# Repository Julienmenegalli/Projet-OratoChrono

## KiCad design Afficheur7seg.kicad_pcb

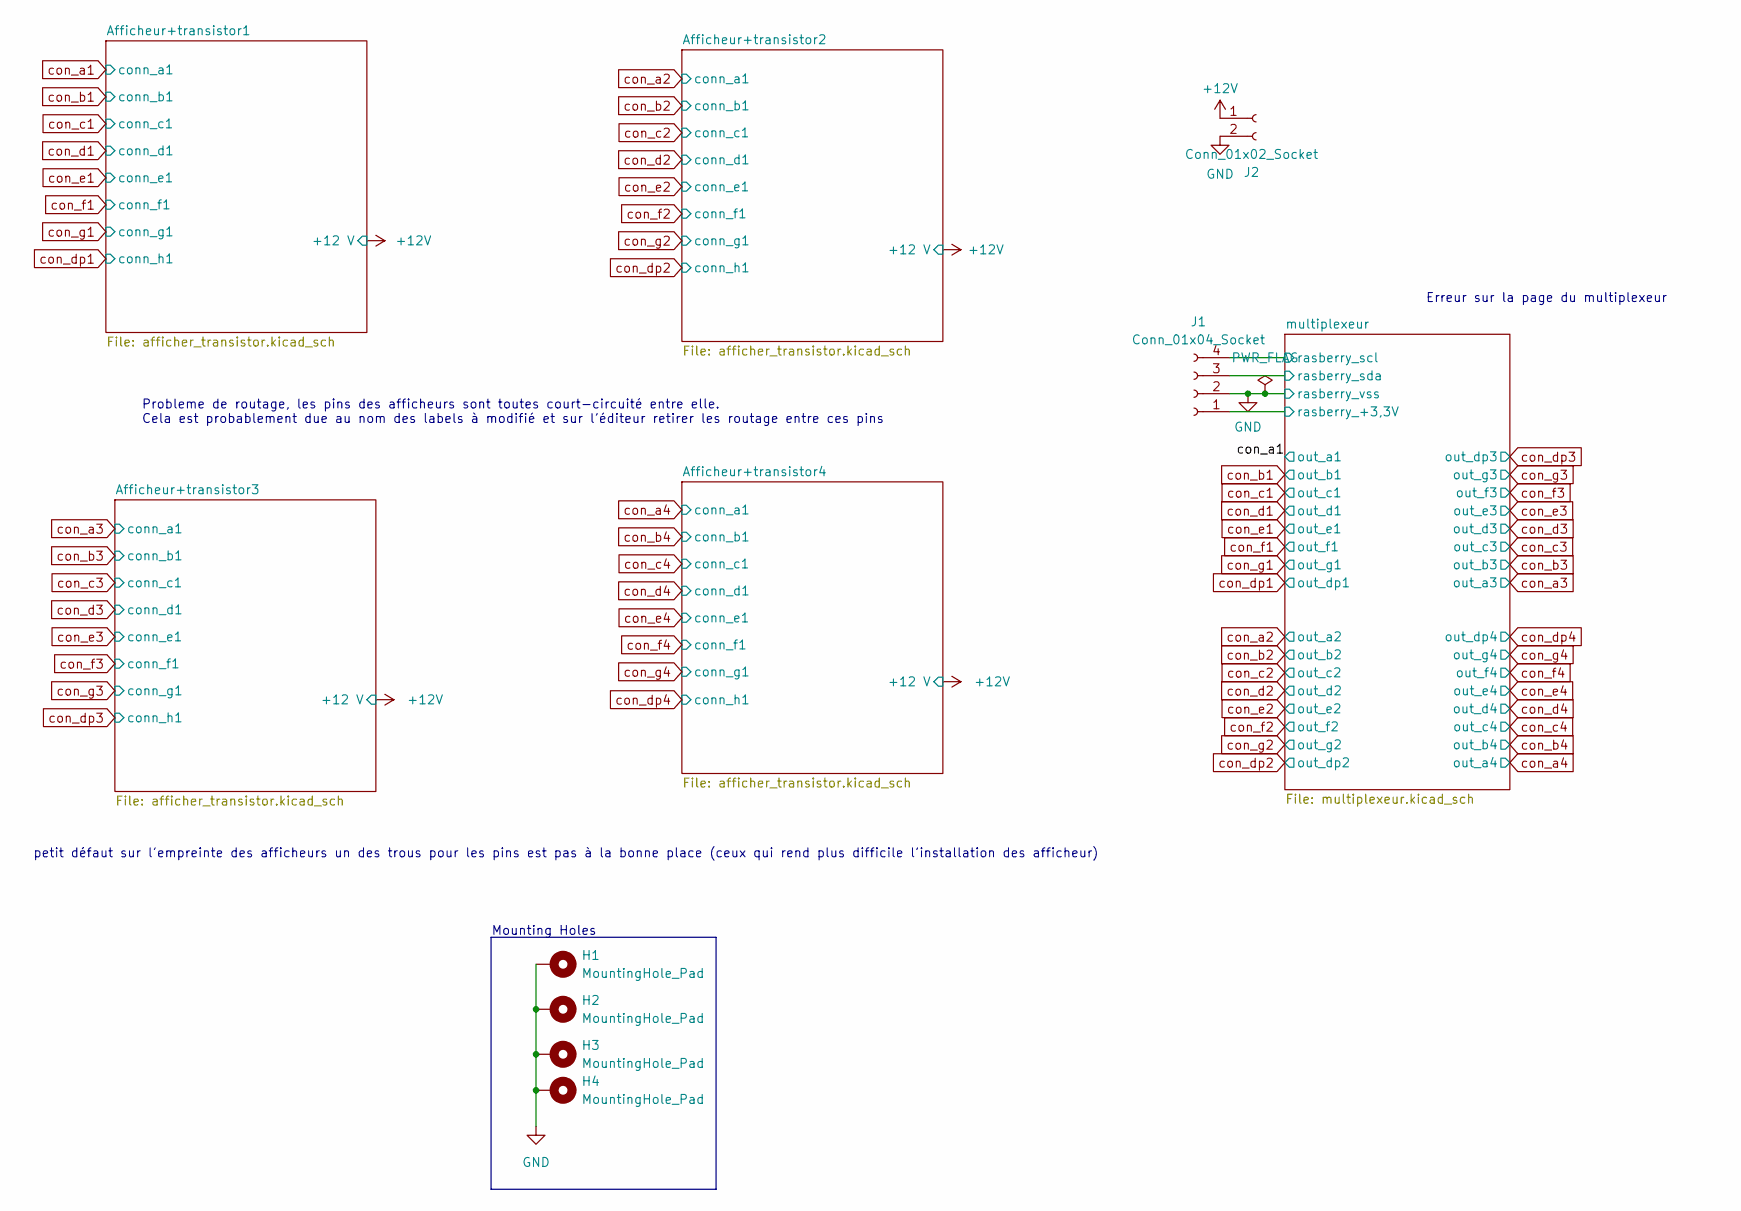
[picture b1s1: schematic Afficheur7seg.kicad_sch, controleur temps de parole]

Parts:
H1, H2, H3, H4: MountingHole_Pad; MountingHole_3.2mm_M3_DIN965_Pad
J1: Conn_01x04_Socket; JST_XH_B4B-XH-A_1x04_P2.50mm_Vertical
J2: Conn_01x02_Socket; JST_XH_B2B-XH-A_1x02_P2.50mm_Vertical

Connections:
+12V: J2.1; also elsewhere on the board
/multiplexeur/rasberry_+3,3V: J1.1; also elsewhere on the board
/multiplexeur/rasberry_scl: J1.4; also elsewhere on the board
/multiplexeur/rasberry_sda: J1.3; also elsewhere on the board
GND: H1.1, H2.1, H3.1, H4.1, J1.2, J2.2; also elsewhere on the board

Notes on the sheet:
petit défaut sur l'empreinte des afficheurs un des trous pour les pins est pas à la bonne place (ceux qui rend plus difficile l'installation des afficheur)
Probleme de routage, les pins des afficheurs sont toutes court-circuité entre elle. Cela est probablement due au nom des labels à modifié et sur l'éditeur retirer les routage entre ces pins
Mounting Holes
Erreur sur la page du multiplexeur

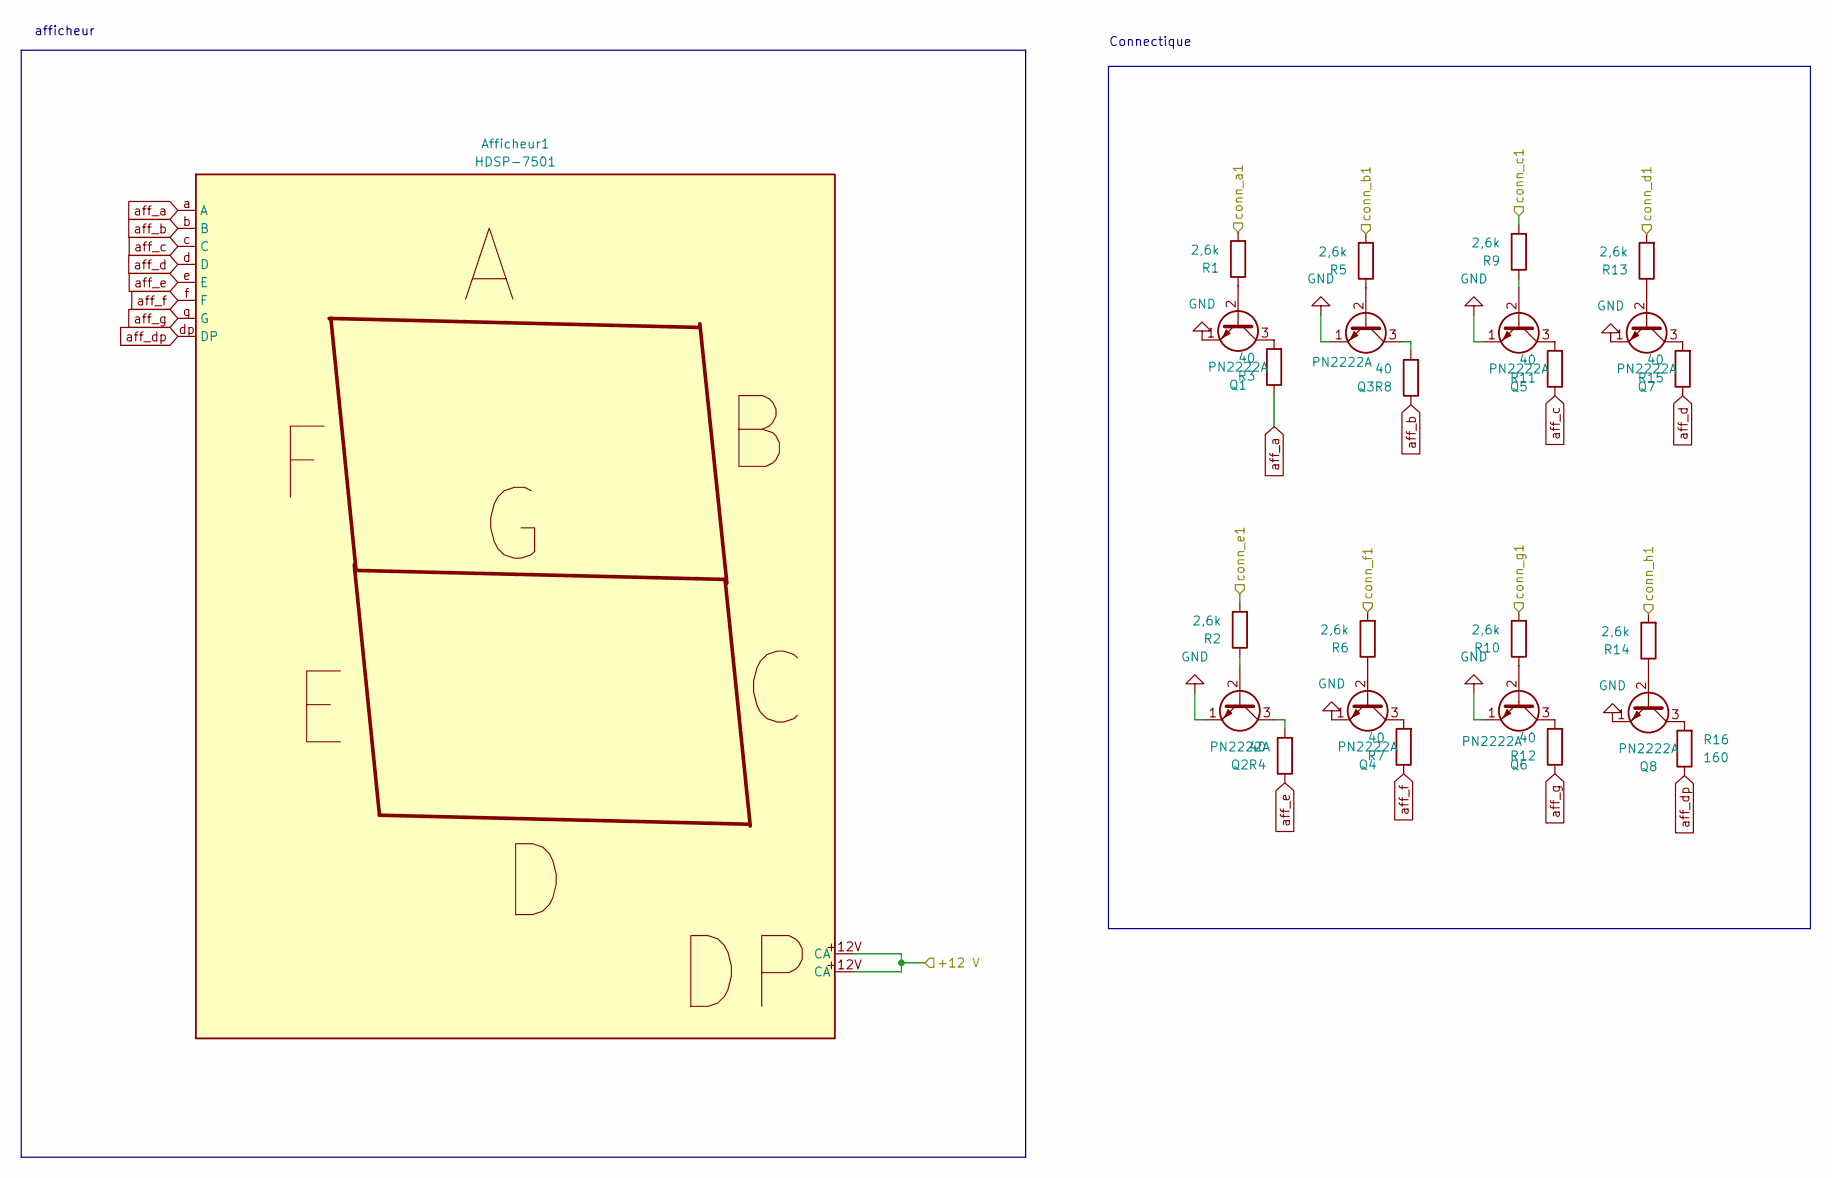
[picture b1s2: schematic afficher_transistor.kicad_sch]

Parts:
Afficheur1: HDSP-7501; Aff_7seg_footprint
Q1, Q2, Q3, Q4, Q5, Q6, Q7, Q8: PN2222A; TO-92_Inline
R1, R2, R5, R6, R9, R10, R13, R14: 2,6k; R_0805_2012Metric
R3, R4, R7, R8, R11, R12, R15: 40; R_Axial_DIN0414_L11.9mm_D4.5mm_P15.24mm_Horizontal
R16: 160; R_Axial_DIN0414_L11.9mm_D4.5mm_P15.24mm_Horizontal

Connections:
+12V: Afficheur1.+12V (CA); also elsewhere on the board
GND: Q1.1 (E), Q2.1 (E), Q3.1 (E), Q4.1 (E), Q5.1 (E), Q6.1 (E), Q7.1 (E), Q8.1 (E); also elsewhere on the board
unnamed: Q1.2 (B), R1.1
unnamed: Q1.3 (C), R3.2
unnamed: Q2.2 (B), R2.1
unnamed: Q2.3 (C), R4.2
unnamed: Q3.2 (B), R5.1
unnamed: Q3.3 (C), R8.2
unnamed: Q4.2 (B), R6.1
unnamed: Q4.3 (C), R7.2
unnamed: Q5.2 (B), R9.1
unnamed: Q5.3 (C), R11.2
unnamed: Q6.2 (B), R10.1
unnamed: Q6.3 (C), R12.2
unnamed: Q7.2 (B), R13.1
unnamed: Q7.3 (C), R15.2
unnamed: Q8.2 (B), R14.1
unnamed: Q8.3 (C), R16.2
aff_a: Afficheur1.a (A), R3.1; also elsewhere on the board
aff_b: Afficheur1.b (B), R8.1; also elsewhere on the board
aff_c: Afficheur1.c (C), R11.1; also elsewhere on the board
aff_d: Afficheur1.d (D), R15.1; also elsewhere on the board
aff_dp: Afficheur1.dp (DP), R16.1; also elsewhere on the board
aff_e: Afficheur1.e (E), R4.1; also elsewhere on the board
aff_f: Afficheur1.f (F), R7.1; also elsewhere on the board
aff_g: Afficheur1.g (G), R12.1; also elsewhere on the board
con_a2: R1.2; also elsewhere on the board
con_b2: R5.2; also elsewhere on the board
con_c2: R9.2; also elsewhere on the board
con_d2: R13.2; also elsewhere on the board
con_dp2: R14.2; also elsewhere on the board
con_e2: R2.2; also elsewhere on the board
con_f2: R6.2; also elsewhere on the board
con_g2: R10.2; also elsewhere on the board

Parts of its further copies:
Afficheur2, Afficheur3, Afficheur4: HDSP-7501; Aff_7seg_footprint
Q9, Q10, Q11, Q12, Q13, Q14, Q15, Q16, Q17, Q18, Q19, Q20, Q21, Q22, Q23, Q24, Q25, Q26, Q27, Q28, Q29, Q30, Q31, Q32: PN2222A; TO-92_Inline
R17, R18, R21, R22, R25, R26, R29, R30, R33, R34, R37, R38, R41, R42, R45, R46, R51, R52, R55, R56, R59, R60, R63, R64: 2,6k; R_0805_2012Metric
R19, R20, R23, R24, R27, R28, R31, R35, R36, R39, R40, R43, R44, R47, R53, R54, R57, R58, R61, R62, R65: 40; R_Axial_DIN0414_L11.9mm_D4.5mm_P15.24mm_Horizontal
R32, R48, R66: 160; R_Axial_DIN0414_L11.9mm_D4.5mm_P15.24mm_Horizontal

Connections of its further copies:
+12V: Afficheur2.+12V (CA), Afficheur3.+12V (CA), Afficheur4.+12V (CA); also elsewhere on the board
GND: Q9.1 (E), Q10.1 (E), Q11.1 (E), Q12.1 (E), Q13.1 (E), Q14.1 (E), Q15.1 (E), Q16.1 (E), Q17.1 (E), Q18.1 (E), Q19.1 (E), Q20.1 (E), Q21.1 (E), Q22.1 (E), Q23.1 (E), Q24.1 (E), Q25.1 (E), Q26.1 (E), Q27.1 (E), Q28.1 (E), Q29.1 (E), Q30.1 (E), Q31.1 (E), Q32.1 (E); also elsewhere on the board
unnamed: Q9.2 (B), R17.1
unnamed: Q9.3 (C), R19.2
unnamed: Q10.2 (B), R18.1
unnamed: Q10.3 (C), R20.2
unnamed: Q11.2 (B), R21.1
unnamed: Q11.3 (C), R24.2
unnamed: Q12.2 (B), R22.1
unnamed: Q12.3 (C), R23.2
unnamed: Q13.2 (B), R25.1
unnamed: Q13.3 (C), R27.2
unnamed: Q14.2 (B), R26.1
unnamed: Q14.3 (C), R28.2
unnamed: Q15.2 (B), R29.1
unnamed: Q15.3 (C), R31.2
unnamed: Q16.2 (B), R30.1
unnamed: Q16.3 (C), R32.2
unnamed: Q17.2 (B), R33.1
unnamed: Q17.3 (C), R35.2
unnamed: Q18.2 (B), R34.1
unnamed: Q18.3 (C), R36.2
unnamed: Q19.2 (B), R37.1
unnamed: Q19.3 (C), R40.2
unnamed: Q20.2 (B), R38.1
unnamed: Q20.3 (C), R39.2
unnamed: Q21.2 (B), R41.1
unnamed: Q21.3 (C), R43.2
unnamed: Q22.2 (B), R42.1
unnamed: Q22.3 (C), R44.2
unnamed: Q23.2 (B), R45.1
unnamed: Q23.3 (C), R47.2
unnamed: Q24.2 (B), R46.1
unnamed: Q24.3 (C), R48.2
unnamed: Q25.2 (B), R51.1
unnamed: Q25.3 (C), R53.2
unnamed: Q26.2 (B), R52.1
unnamed: Q26.3 (C), R54.2
unnamed: Q27.2 (B), R55.1
unnamed: Q27.3 (C), R58.2
unnamed: Q28.2 (B), R56.1
unnamed: Q28.3 (C), R57.2
unnamed: Q29.2 (B), R59.1
unnamed: Q29.3 (C), R61.2
unnamed: Q30.2 (B), R60.1
unnamed: Q30.3 (C), R62.2
unnamed: Q31.2 (B), R63.1
unnamed: Q31.3 (C), R65.2
unnamed: Q32.2 (B), R64.1
unnamed: Q32.3 (C), R66.2
aff_a: Afficheur2.a (A), Afficheur3.a (A), Afficheur4.a (A), R19.1, R35.1, R53.1; also elsewhere on the board
aff_b: Afficheur2.b (B), Afficheur3.b (B), Afficheur4.b (B), R24.1, R40.1, R58.1; also elsewhere on the board
aff_c: Afficheur2.c (C), Afficheur3.c (C), Afficheur4.c (C), R27.1, R43.1, R61.1; also elsewhere on the board
aff_d: Afficheur2.d (D), Afficheur3.d (D), Afficheur4.d (D), R31.1, R47.1, R65.1; also elsewhere on the board
aff_dp: Afficheur2.dp (DP), Afficheur3.dp (DP), Afficheur4.dp (DP), R32.1, R48.1, R66.1; also elsewhere on the board
aff_e: Afficheur2.e (E), Afficheur3.e (E), Afficheur4.e (E), R20.1, R36.1, R54.1; also elsewhere on the board
aff_f: Afficheur2.f (F), Afficheur3.f (F), Afficheur4.f (F), R23.1, R39.1, R57.1; also elsewhere on the board
aff_g: Afficheur2.g (G), Afficheur3.g (G), Afficheur4.g (G), R28.1, R44.1, R62.1; also elsewhere on the board
con_a1: R51.2; also elsewhere on the board
con_a3: R17.2; also elsewhere on the board
con_a4: R33.2; also elsewhere on the board
con_b1: R55.2; also elsewhere on the board
con_b3: R21.2; also elsewhere on the board
con_b4: R37.2; also elsewhere on the board
con_c1: R59.2; also elsewhere on the board
con_c3: R25.2; also elsewhere on the board
con_c4: R41.2; also elsewhere on the board
con_d1: R63.2; also elsewhere on the board
con_d3: R29.2; also elsewhere on the board
con_d4: R45.2; also elsewhere on the board
con_dp1: R64.2; also elsewhere on the board
con_dp3: R30.2; also elsewhere on the board
con_dp4: R46.2; also elsewhere on the board
con_e1: R52.2; also elsewhere on the board
con_e3: R18.2; also elsewhere on the board
con_e4: R34.2; also elsewhere on the board
con_f1: R56.2; also elsewhere on the board
con_f3: R22.2; also elsewhere on the board
con_f4: R38.2; also elsewhere on the board
con_g1: R60.2; also elsewhere on the board
con_g3: R26.2; also elsewhere on the board
con_g4: R42.2; also elsewhere on the board

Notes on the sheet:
afficheur
Connectique

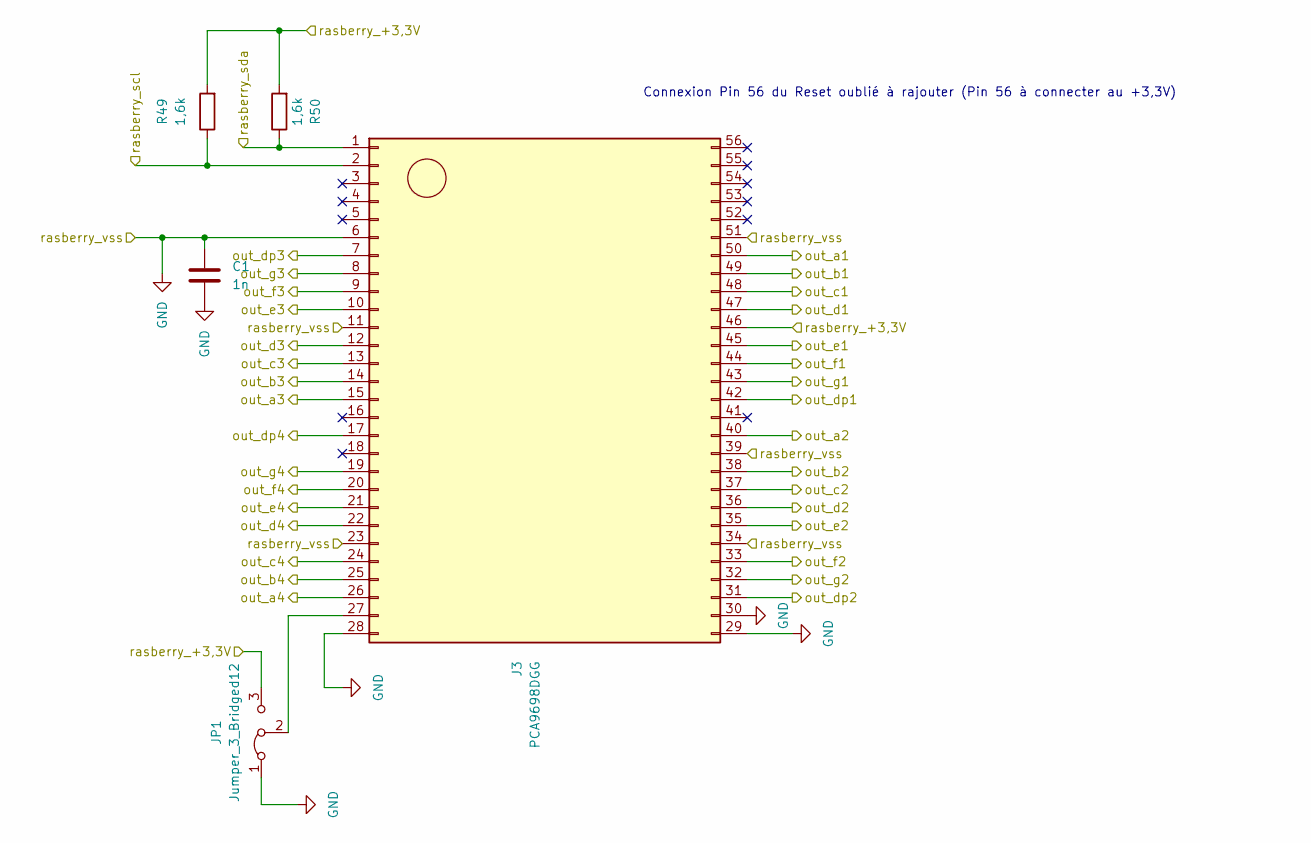
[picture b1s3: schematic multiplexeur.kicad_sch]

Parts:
C1: 1n; C_0603_1608Metric_Pad1.08x0.95mm_HandSolder
J3: PCA9698DGG; TSSOP-56_8x14mm_P0.5mm
JP1: Jumper_3_Bridged12; PinHeader_1x03_P2.54mm_Vertical
R49, R50: 1,6k; R_0805_2012Metric

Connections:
/multiplexeur/rasberry_+3,3V: J3.46 (Pin_b11), JP1.3 (B), R49.2, R50.2; also elsewhere on the board
/multiplexeur/rasberry_scl: J3.2 (Pin_a2), R49.1; also elsewhere on the board
/multiplexeur/rasberry_sda: J3.1 (Pin_a1), R50.1; also elsewhere on the board
GND: C1.1, C1.2, J3.6 (Pin_a6), J3.11 (Pin_a11), J3.23 (Pin_a23), J3.28 (Pin_a28), J3.29 (Pin_b28), J3.30 (Pin_b27), J3.34 (Pin_b23), J3.39 (Pin_b18), J3.51 (Pin_b6), JP1.1 (A); also elsewhere on the board
unnamed: J3.27 (Pin_a27), JP1.2 (C)
con_a1: J3.50 (Pin_b7); also elsewhere on the board
con_a2: J3.40 (Pin_b17); also elsewhere on the board
con_a3: J3.15 (Pin_a15); also elsewhere on the board
con_a4: J3.26 (Pin_a26); also elsewhere on the board
con_b1: J3.49 (Pin_b8); also elsewhere on the board
con_b2: J3.38 (Pin_b19); also elsewhere on the board
con_b3: J3.14 (Pin_a14); also elsewhere on the board
con_b4: J3.25 (Pin_a25); also elsewhere on the board
con_c1: J3.48 (Pin_b9); also elsewhere on the board
con_c2: J3.37 (Pin_b20); also elsewhere on the board
con_c3: J3.13 (Pin_a13); also elsewhere on the board
con_c4: J3.24 (Pin_a24); also elsewhere on the board
con_d1: J3.47 (Pin_b10); also elsewhere on the board
con_d2: J3.36 (Pin_b21); also elsewhere on the board
con_d3: J3.12 (Pin_a12); also elsewhere on the board
con_d4: J3.22 (Pin_a22); also elsewhere on the board
con_dp1: J3.42 (Pin_b15); also elsewhere on the board
con_dp2: J3.31 (Pin_b26); also elsewhere on the board
con_dp3: J3.7 (Pin_a7); also elsewhere on the board
con_dp4: J3.17 (Pin_a17); also elsewhere on the board
con_e1: J3.45 (Pin_b12); also elsewhere on the board
con_e2: J3.35 (Pin_b22); also elsewhere on the board
con_e3: J3.10 (Pin_a10); also elsewhere on the board
con_e4: J3.21 (Pin_a21); also elsewhere on the board
con_f1: J3.44 (Pin_b13); also elsewhere on the board
con_f2: J3.33 (Pin_b24); also elsewhere on the board
con_f3: J3.9 (Pin_a9); also elsewhere on the board
con_f4: J3.20 (Pin_a20); also elsewhere on the board
con_g1: J3.43 (Pin_b14); also elsewhere on the board
con_g2: J3.32 (Pin_b25); also elsewhere on the board
con_g3: J3.8 (Pin_a8); also elsewhere on the board
con_g4: J3.19 (Pin_a19); also elsewhere on the board

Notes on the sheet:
Connexion Pin 56 du Reset oublié à rajouter (Pin 56 à connecter au +3,3V)

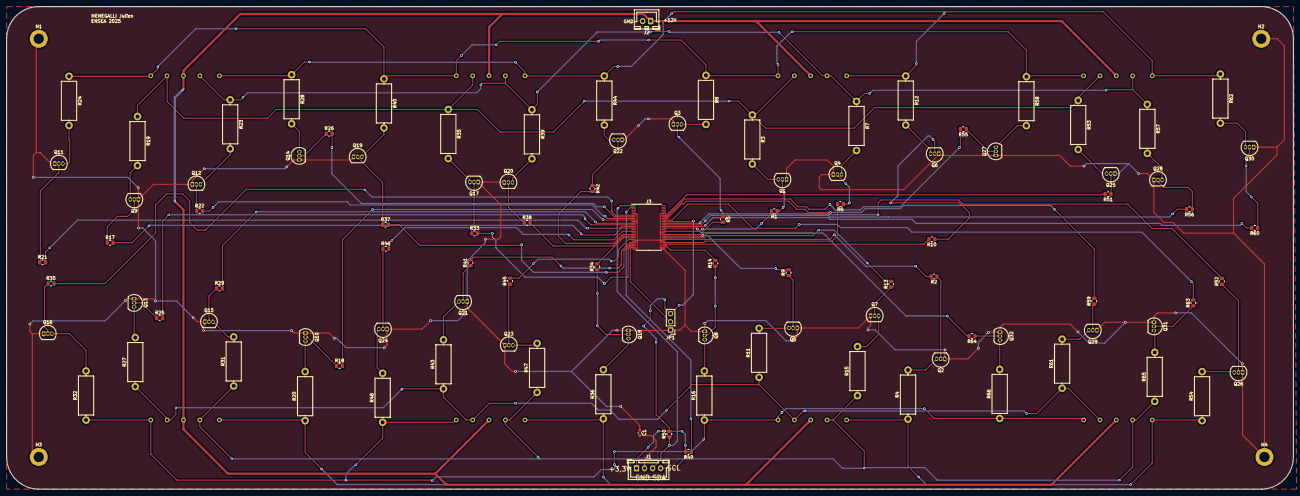
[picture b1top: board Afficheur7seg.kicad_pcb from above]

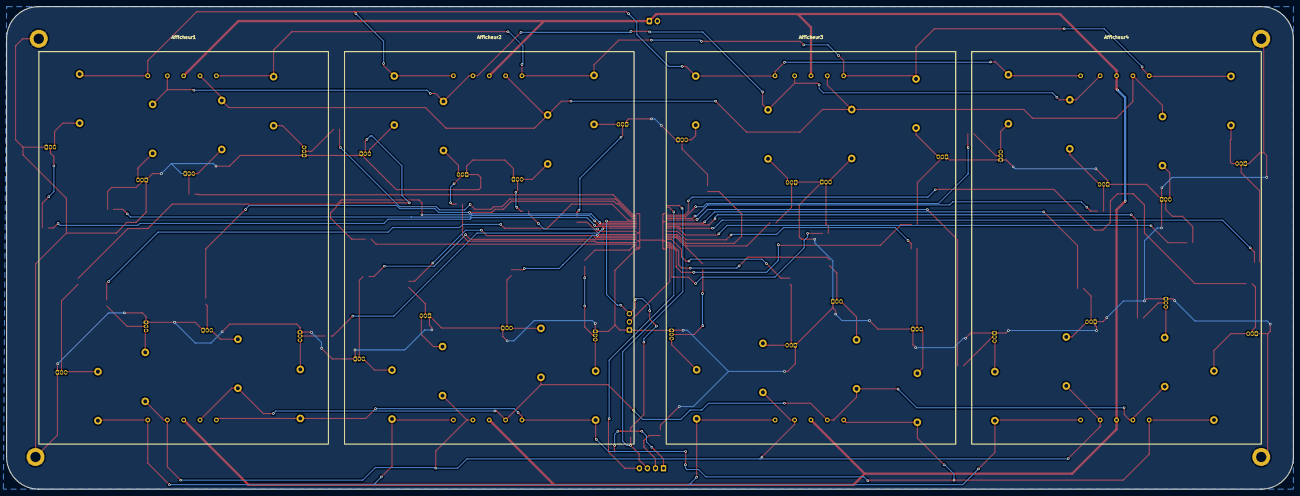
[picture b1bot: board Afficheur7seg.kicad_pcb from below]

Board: 2 copper layers, 400.0 x 150.0 mm, 111 parts (4 on the bottom side), 110 nets.
